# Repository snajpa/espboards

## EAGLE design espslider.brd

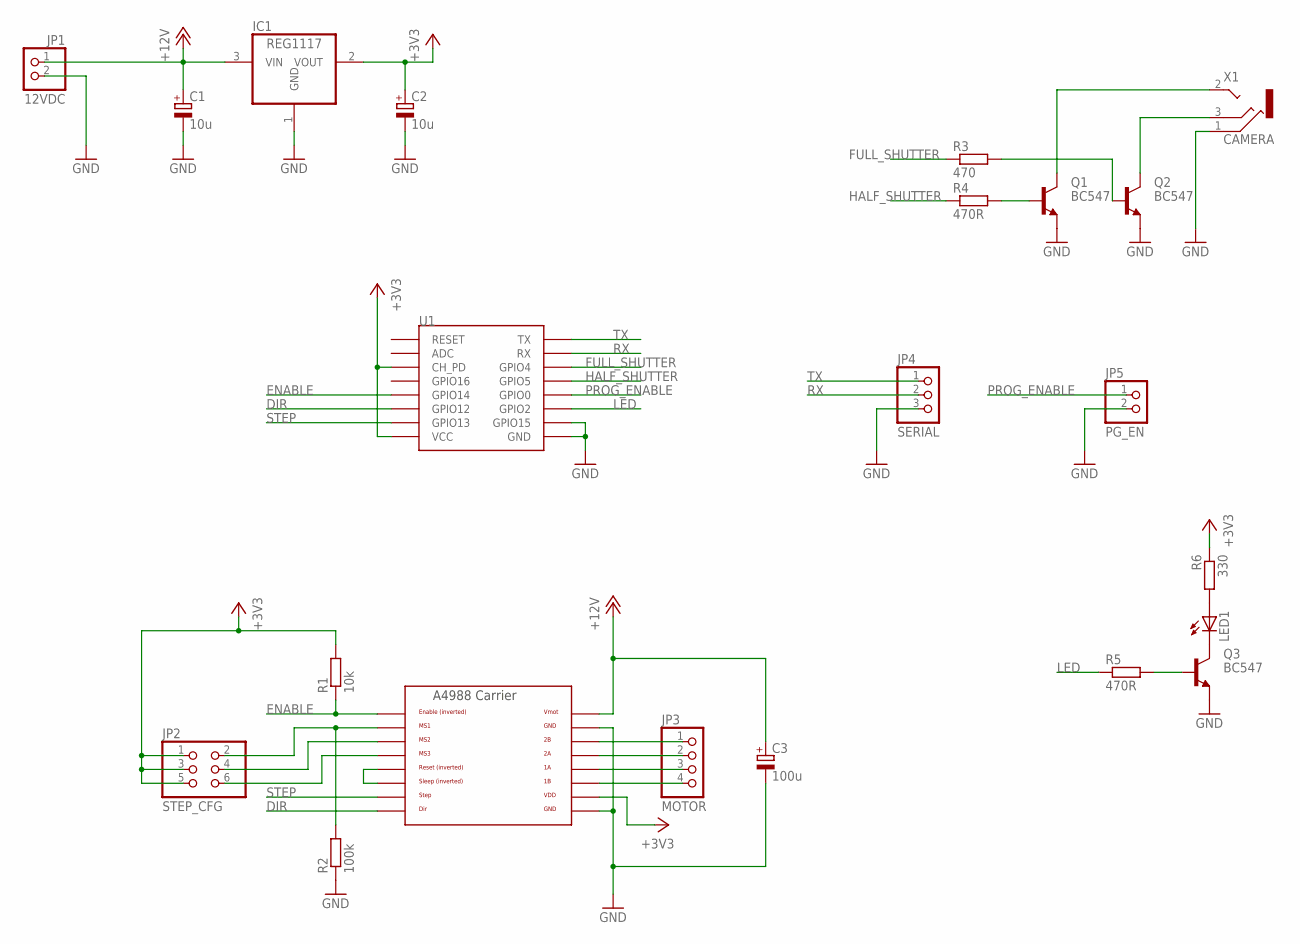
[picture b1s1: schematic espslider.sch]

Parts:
C1, C2: 10u; E5-5; MPN T491C107K010AT
C3: 100u; E5-5
IC1: REG1117; SOT223
JP1: 12VDC; 1X02
JP2: STEP_CFG; 2X03
JP3: MOTOR; 1X04
JP4: SERIAL; 1X03
JP5: PG_EN; 1X02
LED1: LED3MM
Q1, Q2, Q3: BC547; TO92
R1: 10k; 0207/7
R2: 100k; 0207/15
R3: 470; 0207/7
R4, R5: 470R; 0207/7
R6: 330; 0207/7
U1: ESP12SMD; ESP12-SMD
U2: A4988BREAKOUT
X1: CAMERA; 1501_05

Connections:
+3V3: C2.+, IC1.2 (VOUT), JP2.1, JP2.3, JP2.5, R1.2, R6.1, U1.CH_PD, U1.VCC, U2.VDD
+12V: C1.+, C3.+, IC1.3 (VIN), JP1.1, U2.VMOT
DIR: U1.GPIO12, U2.DIR
ENABLE: R1.1, U1.GPIO14, U2.EN
FULL_SHUTTER: R3.1, U1.GPIO4
GND: C1.-, C2.-, C3.-, IC1.1 (GND), JP1.2, JP4.3, JP5.2, Q1.1 (E), Q2.1 (E), Q3.1 (E), R2.1, U1.GND, U1.GPIO15, U2.GND, U2.GND@0 (GND), X1.1
HALF_SHUTTER: R4.1, U1.GPIO5
LED: R5.1, U1.GPIO2
unnamed: Q2.3 (C), X1.3
unnamed: Q2.2 (B), R3.2
unnamed: Q1.2 (B), R4.2
unnamed: Q1.3 (C), X1.2
unnamed: JP2.2, R2.2, U2.MS1
unnamed: JP2.4, U2.MS2
unnamed: JP2.6, U2.MS3
unnamed: LED1.A, R6.2
unnamed: U2.RST, U2.SLP (SLEEP)
unnamed: JP3.1, U2.2B
unnamed: JP3.2, U2.2A
unnamed: JP3.3, U2.1A
unnamed: JP3.4, U2.1B
unnamed: LED1.K (C), Q3.3 (C)
unnamed: Q3.2 (B), R5.2
PROG_ENABLE: JP5.1, U1.GPIO0
RX: JP4.2, U1.RXD0 (RX)
STEP: U1.GPIO13, U2.STEP
TX: JP4.1, U1.TXD0 (TX)

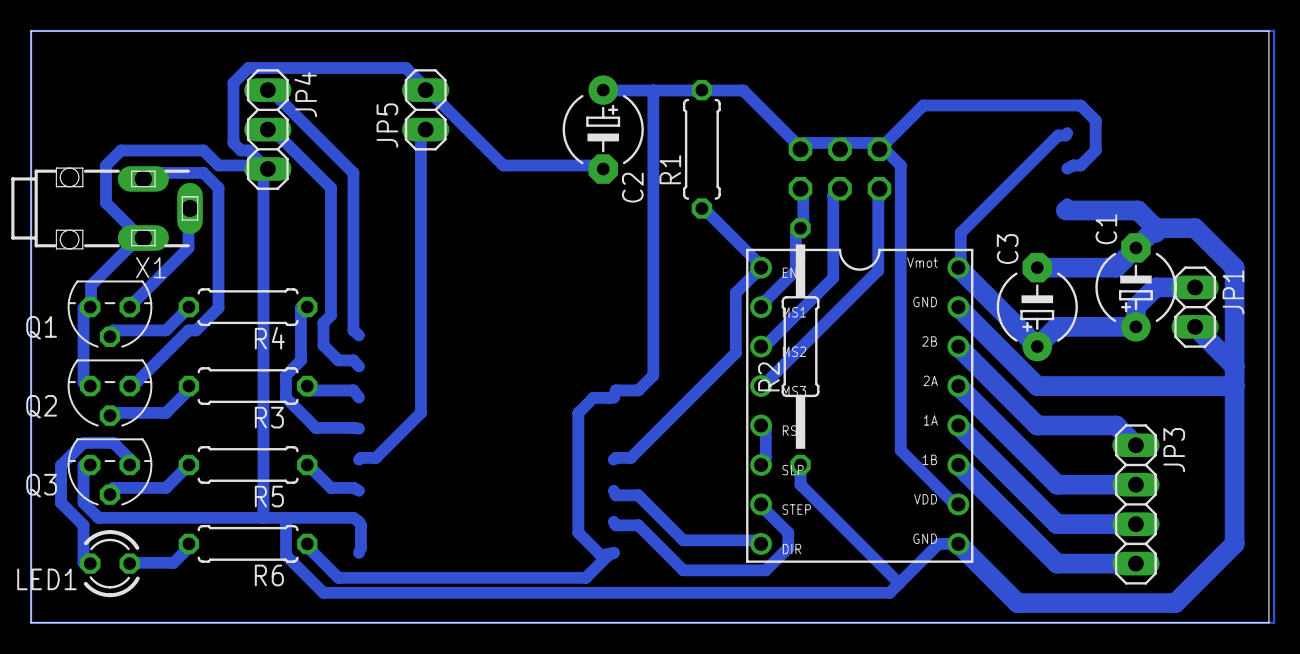
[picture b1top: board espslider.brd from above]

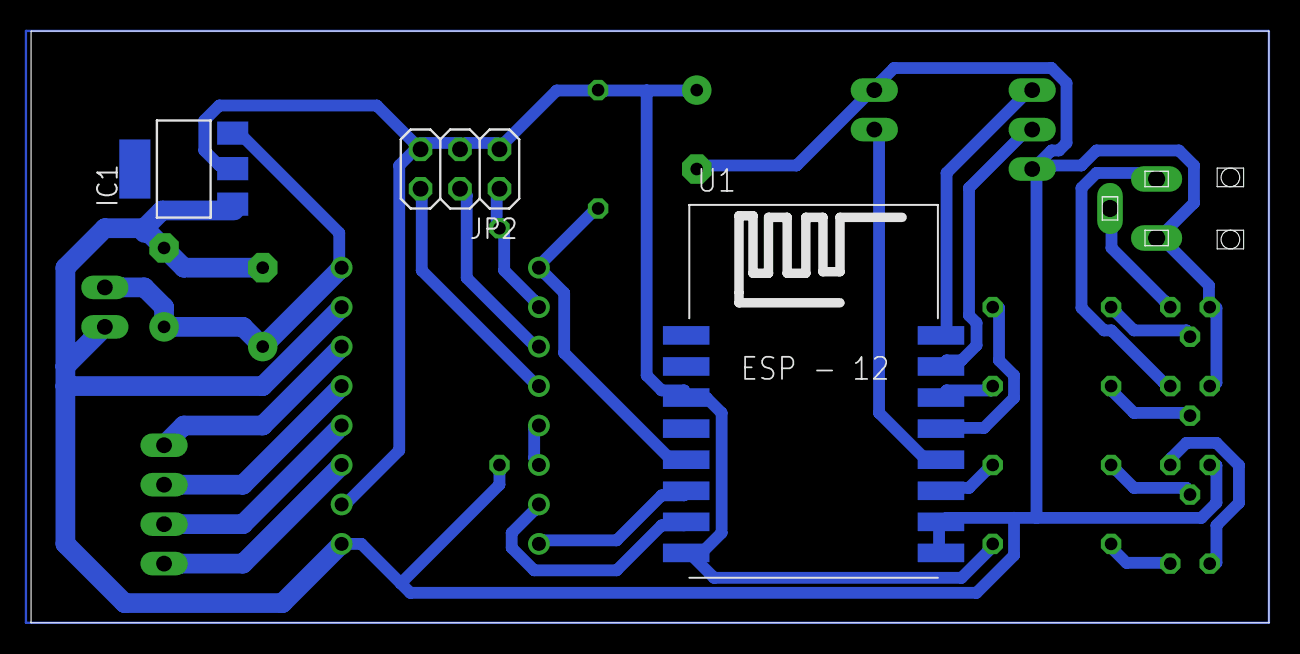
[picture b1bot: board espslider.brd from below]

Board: 2 copper layers, 79.7 x 38.1 mm, 22 parts (3 on the bottom side), 27 nets.

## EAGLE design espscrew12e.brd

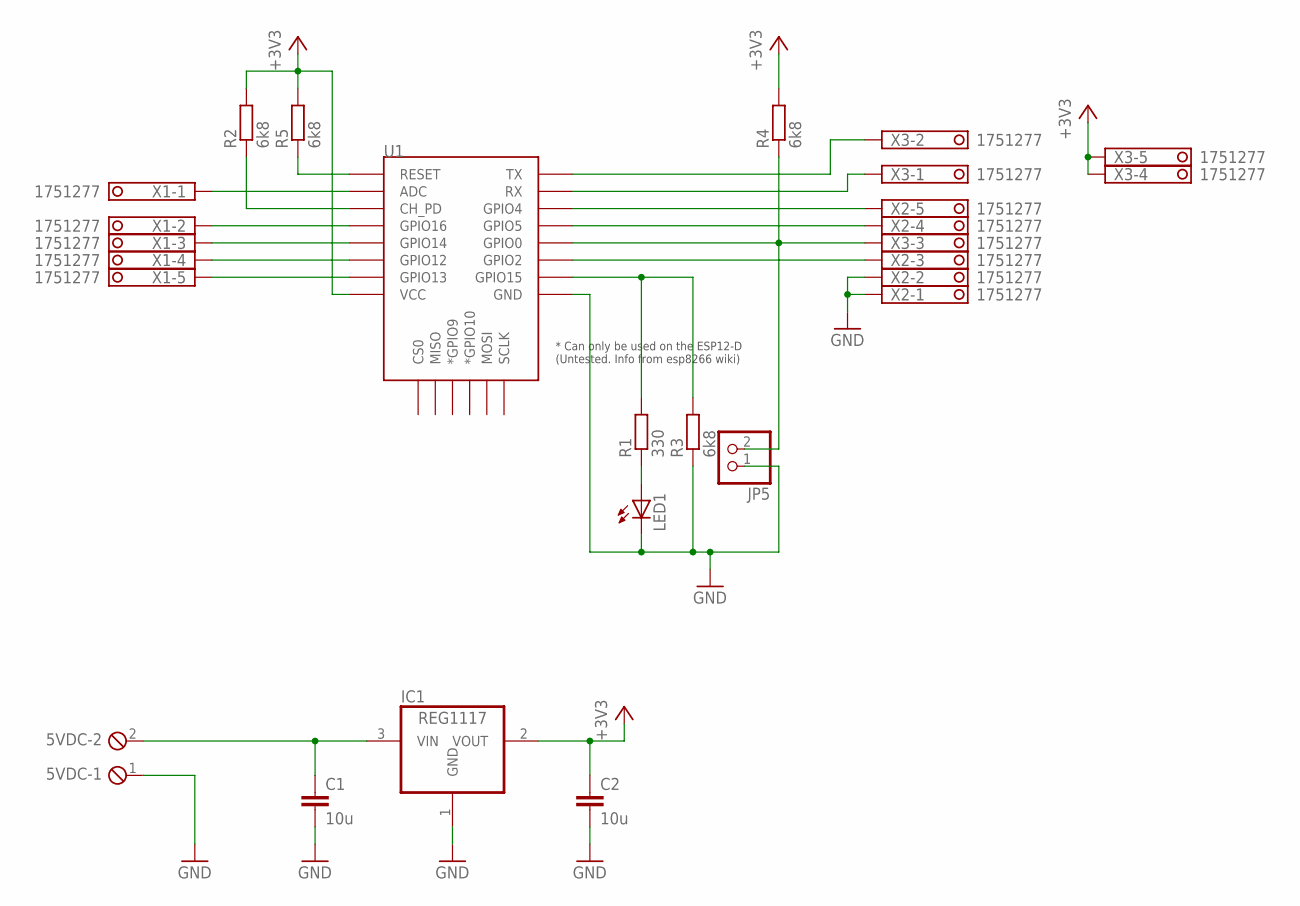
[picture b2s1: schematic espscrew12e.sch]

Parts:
5VDC: MPT2; 2POL254
C1, C2: 10u; C1206K
IC1: REG1117; SOT223
JP5: PINHD-1X2; 1X02
LED1: LEDSML1206; SML1206
R1: 330; R1206
R2, R3, R4, R5: 6k8; R1206
U1: ESP12ESMD; ESP12E-SMD
X1, X2, X3: 1751277

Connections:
+3V3: C2.1, IC1.2 (VOUT), R2.2, R4.2, R5.2, U1.VCC, X3.4, X3.5
GND: 5VDC.1, C1.2, C2.2, IC1.1 (GND), JP5.1, LED1.C, R3.1, U1.GND, X2.1, X2.2
unnamed: 5VDC.2, C1.1, IC1.3 (VIN)
unnamed: LED1.A, R1.1
unnamed: R5.1, U1.RESET
unnamed: U1.ADC, X1.1
unnamed: R2.1, U1.CH_PD
unnamed: U1.GPIO16, X1.2
unnamed: U1.GPIO14, X1.3
unnamed: U1.GPIO12, X1.4
unnamed: U1.GPIO13, X1.5
unnamed: U1.TXD0 (TX), X3.2
unnamed: U1.RXD0 (RX), X3.1
unnamed: U1.GPIO4, X2.5
unnamed: U1.GPIO5, X2.4
unnamed: JP5.2, R4.1, U1.GPIO0, X3.3
unnamed: U1.GPIO2, X2.3
unnamed: R1.2, R3.2, U1.GPIO15

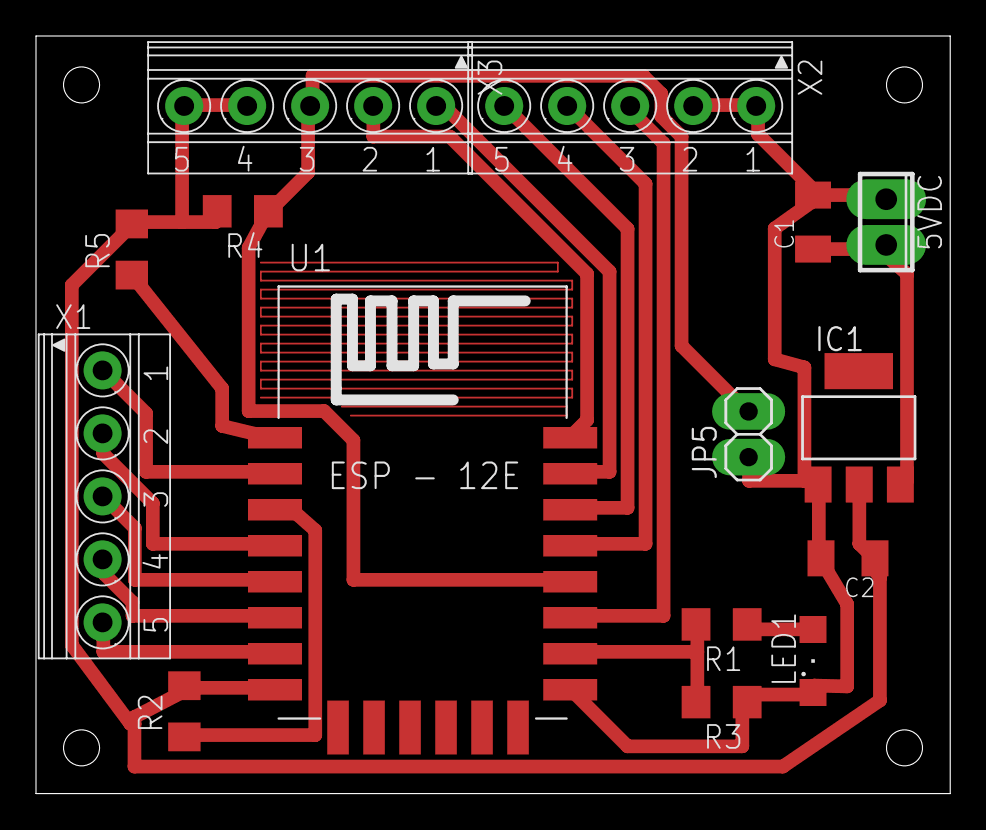
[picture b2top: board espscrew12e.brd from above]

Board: 2 copper layers, 50.8 x 42.1 mm, 15 parts (0 on the bottom side), 18 nets.

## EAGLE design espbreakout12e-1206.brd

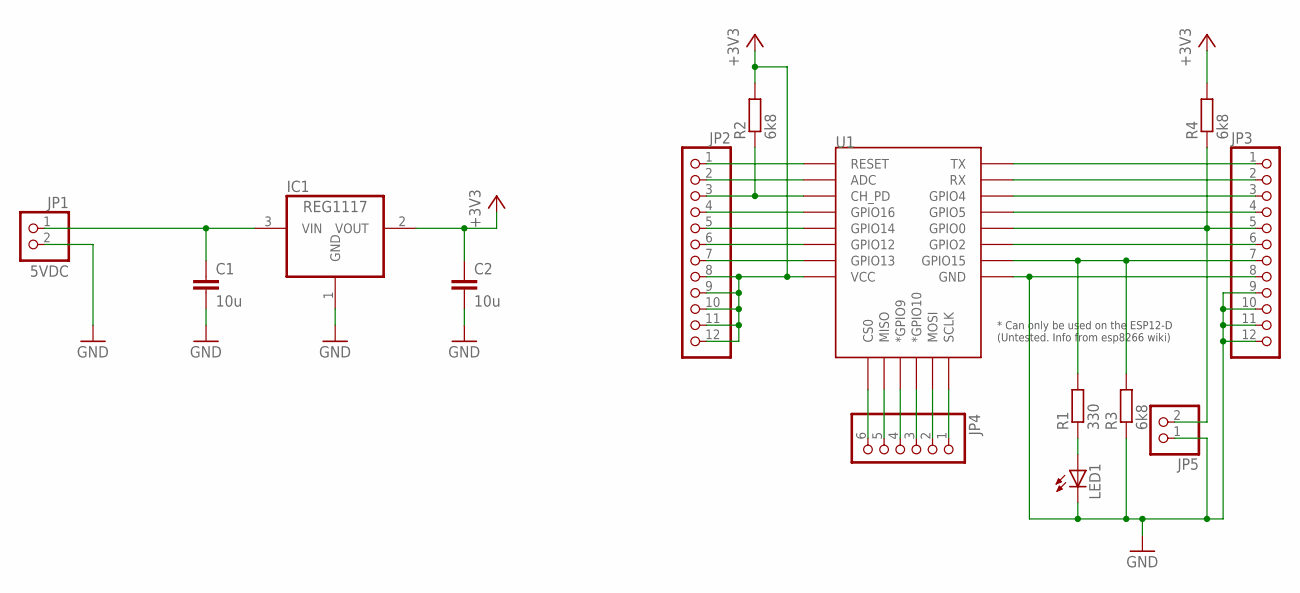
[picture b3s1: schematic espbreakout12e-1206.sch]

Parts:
C1, C2: 10u; C1206K
IC1: REG1117; SOT223
JP1: 5VDC; 1X02
JP2, JP3: PINHD-1X12; 1X12
JP4: PINHD-1X6; 1X06
JP5: PINHD-1X2; 1X02
LED1: LEDSML1206; SML1206
R1: 330; R1206
R2, R3, R4: 6k8; R1206
U1: ESP12ESMD; ESP12E-SMD

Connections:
+3V3: C2.1, IC1.2 (VOUT), JP2.8, JP2.9, JP2.10, JP2.11, JP2.12, R2.2, R4.2, U1.VCC
GND: C1.2, C2.2, IC1.1 (GND), JP1.2, JP3.8, JP3.9, JP3.10, JP3.11, JP3.12, JP5.1, LED1.C, R3.1, U1.GND
unnamed: C1.1, IC1.3 (VIN), JP1.1
unnamed: LED1.A, R1.1
unnamed: JP2.1, U1.RESET
unnamed: JP2.2, U1.ADC
unnamed: JP2.3, R2.1, U1.CH_PD
unnamed: JP2.4, U1.GPIO16
unnamed: JP2.5, U1.GPIO14
unnamed: JP2.6, U1.GPIO12
unnamed: JP2.7, U1.GPIO13
unnamed: JP3.1, U1.TXD0 (TX)
unnamed: JP3.2, U1.RXD0 (RX)
unnamed: JP3.3, U1.GPIO4
unnamed: JP3.4, U1.GPIO5
unnamed: JP3.5, JP5.2, R4.1, U1.GPIO0
unnamed: JP3.6, U1.GPIO2
unnamed: JP3.7, R1.2, R3.2, U1.GPIO15
unnamed: JP4.1, U1.SCLK
unnamed: JP4.2, U1.MOSI
unnamed: JP4.3, U1.GPIO10 (*GPIO10)
unnamed: JP4.4, U1.GPIO9 (*GPIO9)
unnamed: JP4.5, U1.MISO
unnamed: JP4.6, U1.CS0

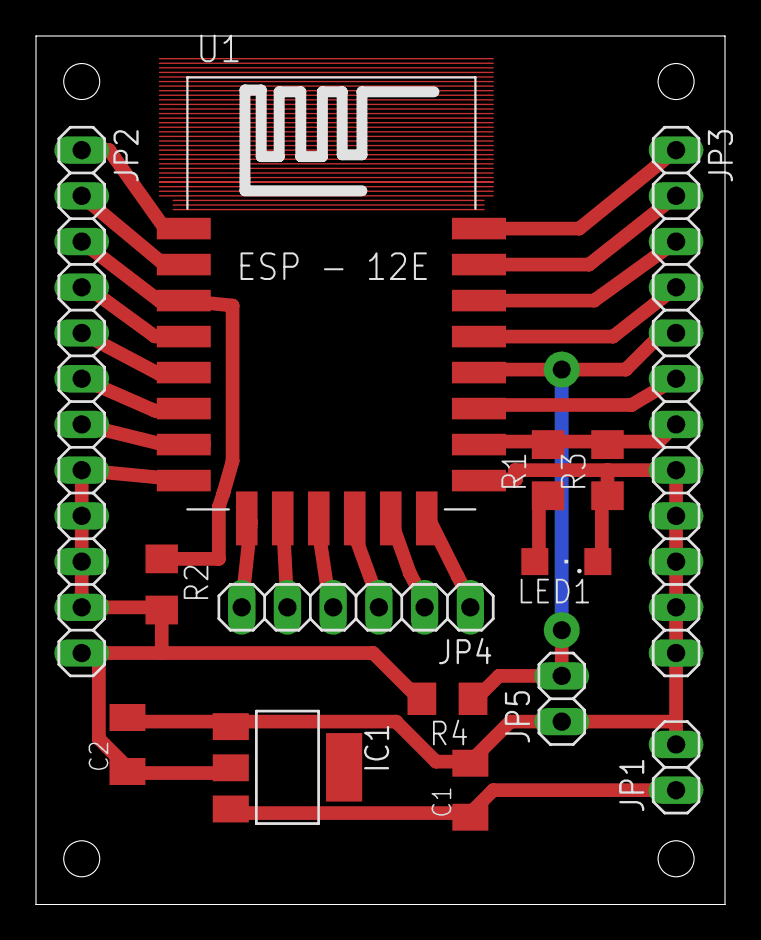
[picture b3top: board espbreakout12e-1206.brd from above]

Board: 2 copper layers, 38.3 x 48.2 mm, 14 parts (0 on the bottom side), 24 nets.

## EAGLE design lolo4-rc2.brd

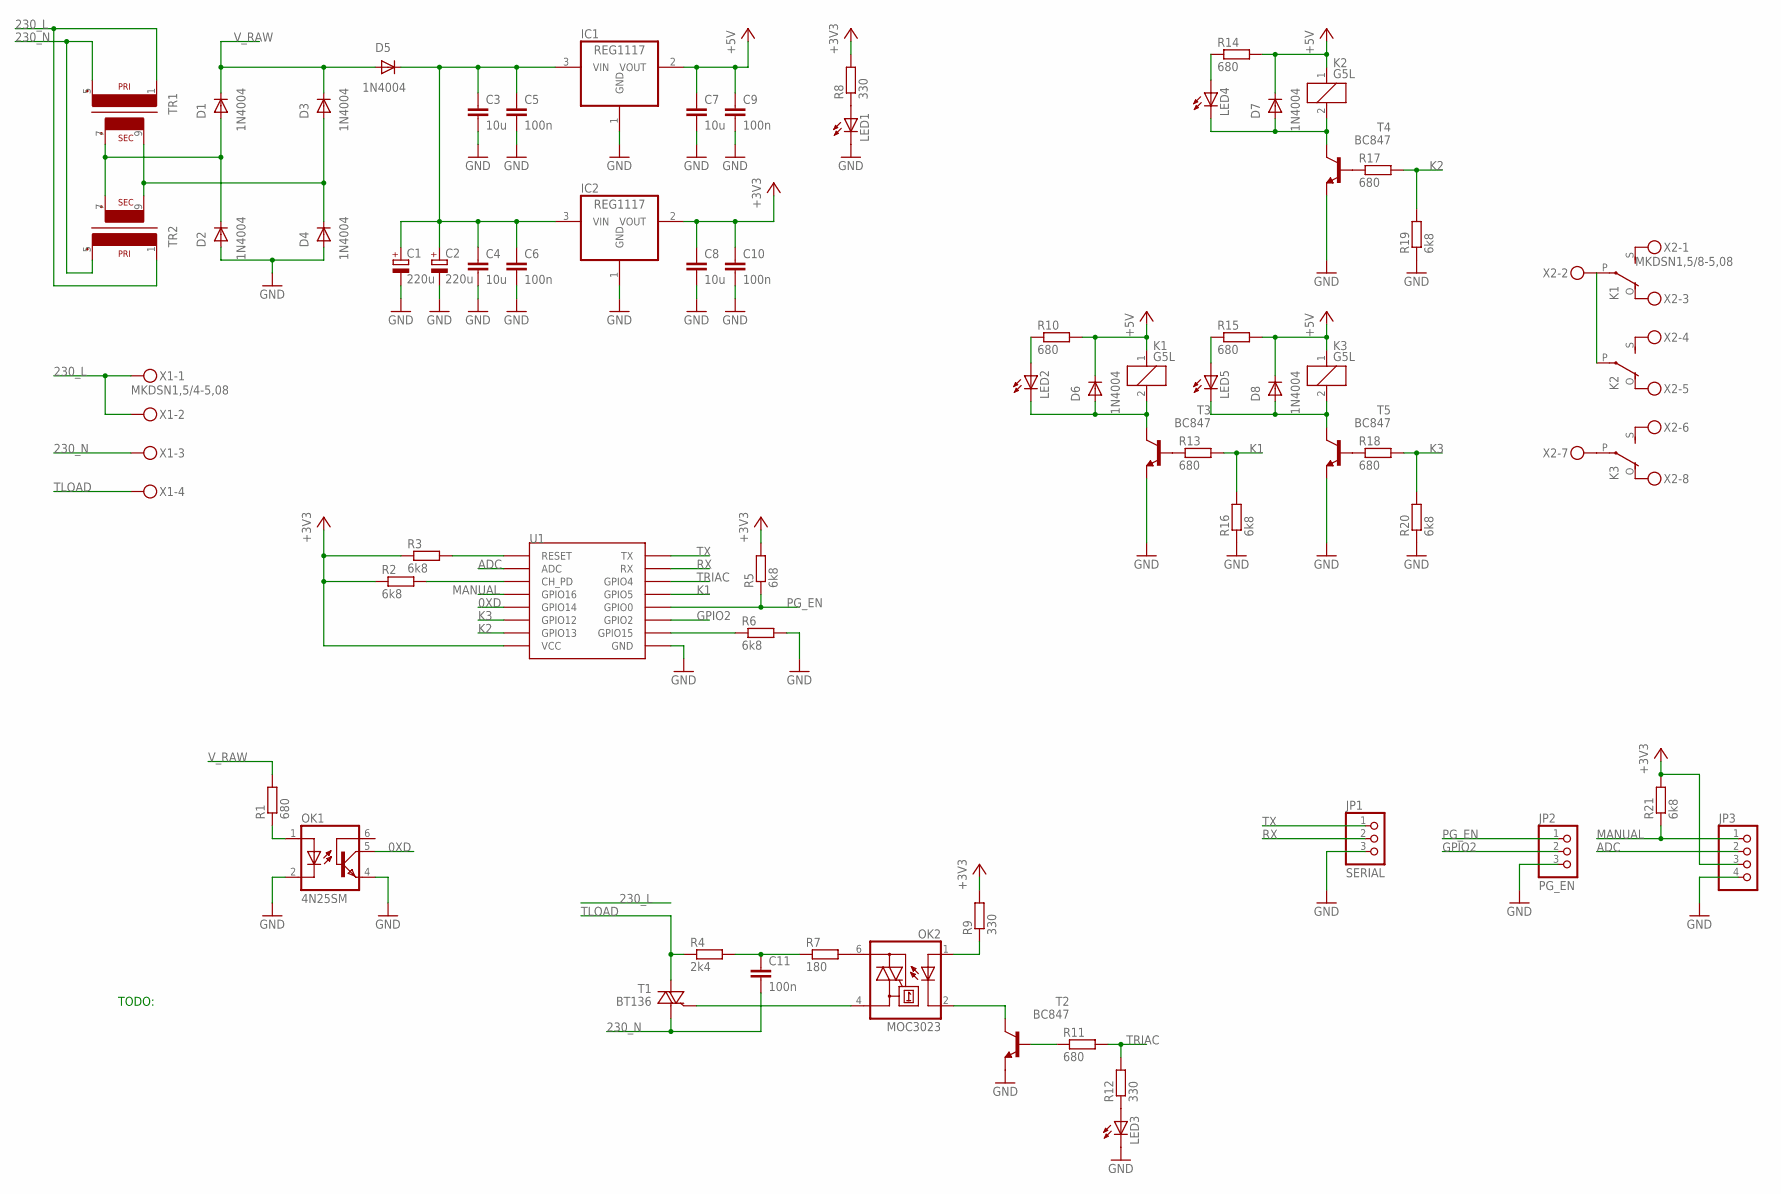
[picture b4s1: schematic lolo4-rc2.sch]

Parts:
C1, C2: 220u; SANYO-OSCON_SMD_E7
C3, C4, C7, C8: 10u; C1206
C5, C6, C9, C10: 100n; C1206
C11: 100n; C150-054X183
D1, D2, D3, D4, D5, D6, D7, D8: 1N4004; DO41-10
IC1, IC2: REG1117; SOT223
JP1: SERIAL; 1X03
JP2: PG_EN; 1X03
JP3: PINHD-1X4; 1X04
K1, K2, K3: G5L; G5LE
LED1, LED2, LED3, LED4, LED5: LEDSML1206; SML1206
OK1: 4N25SM; DIL6-SMD
OK2: MOC3023; DIL6-SMD
R1, R10, R11, R13, R14, R15, R17, R18: 680; R1206
R2, R3, R5, R6, R16, R19, R20, R21: 6k8; R1206
R4: 2k4; 0207/7
R7: 180; 0207/7
R8, R9, R12: 330; R1206
T1: BT136; TO220AB
T2, T3, T4, T5: BC847; SOT23
TR1, TR2: VR11
U1: ESP12SMD; ESP12-SMD
X1: MKDSN1,5/4-5,08
X2: MKDSN1,5/8-5,08

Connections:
0XD: OK1.5 (COL), U1.GPIO14
230_L: TR1.1, TR2.1, X1.1, X1.2
230_N: C11.2, T1.1 (A1), TR1.5 (P2), TR2.5 (P2), X1.3
+3V3: C8.1, C10.1, IC2.2 (VOUT), JP3.3, R2.1, R3.1, R5.2, R8.2, R9.2, R21.2, U1.VCC
+5V: C7.1, C9.1, D6.C, D7.C, D8.C, IC1.2 (VOUT), K1.1, K2.1, K3.1, R10.2, R14.2, R15.2
ADC: JP3.2, U1.ADC
GND: C1.-, C2.-, C3.2, C4.2, C5.2, C6.2, C7.2, C8.2, C9.2, C10.2, D2.A, D4.A, IC1.1 (GND), IC2.1 (GND), JP1.3, JP2.3, JP3.4, LED1.C, LED3.C, OK1.2 (C), OK1.4 (EMI), R6.2, R16.1, R19.1, R20.1, T2.2 (E), T3.2 (E), T4.2 (E), T5.2 (E), U1.GND
GPIO2: JP2.2, U1.GPIO2
K1: R13.2, R16.2, U1.GPIO5
K2: R17.2, R19.2, U1.GPIO13
K3: R18.2, R20.2, U1.GPIO12
MANUAL: JP3.1, R21.1, U1.GPIO16
unnamed: K1.S, X2.1
unnamed: K1.P, K2.P, X2.2
unnamed: K1.O, X2.3
unnamed: K2.S, X2.4
unnamed: K2.O, X2.5
unnamed: K3.P, X2.7
unnamed: K3.S, X2.6
unnamed: LED1.A, R8.1
unnamed: K3.O, X2.8
unnamed: D1.A, D2.C, TR1.7 (S3), TR2.7 (S3)
unnamed: D3.A, D4.C, TR1.9 (S4), TR2.9 (S4)
unnamed: R2.2, U1.CH_PD
unnamed: R6.1, U1.GPIO15
unnamed: R3.2, U1.RESET
unnamed: LED3.A, R12.1
unnamed: R13.1, T3.1 (B)
unnamed: R18.1, T5.1 (B)
unnamed: D7.A, K2.2, LED4.C, T4.3 (C)
unnamed: LED4.A, R14.1
unnamed: R17.1, T4.1 (B)
unnamed: D6.A, K1.2, LED2.C, T3.3 (C)
unnamed: OK1.1 (A), R1.1
unnamed: R11.1, T2.1 (B)
unnamed: D8.A, K3.2, LED5.C, T5.3 (C)
unnamed: LED2.A, R10.1
unnamed: OK2.4 (A1), T1.3 (G)
unnamed: OK2.6 (A2), R7.2
unnamed: C11.1, R4.2, R7.1
unnamed: OK2.2 (C), T2.3 (C)
unnamed: OK2.1 (A), R9.1
unnamed: LED5.A, R15.1
PG_EN: JP2.1, R5.1, U1.GPIO0
RX: JP1.2, U1.RXD0 (RX)
TLOAD: R4.1, T1.2 (A2), X1.4
TRIAC: R11.2, R12.2, U1.GPIO4
TX: JP1.1, U1.TXD0 (TX)
V: C1.+, C2.+, C3.1, C4.1, C5.1, C6.1, D5.C, IC1.3 (VIN), IC2.3 (VIN)
V_RAW: D1.C, D3.C, D5.A, R1.2

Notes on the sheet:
TODO:

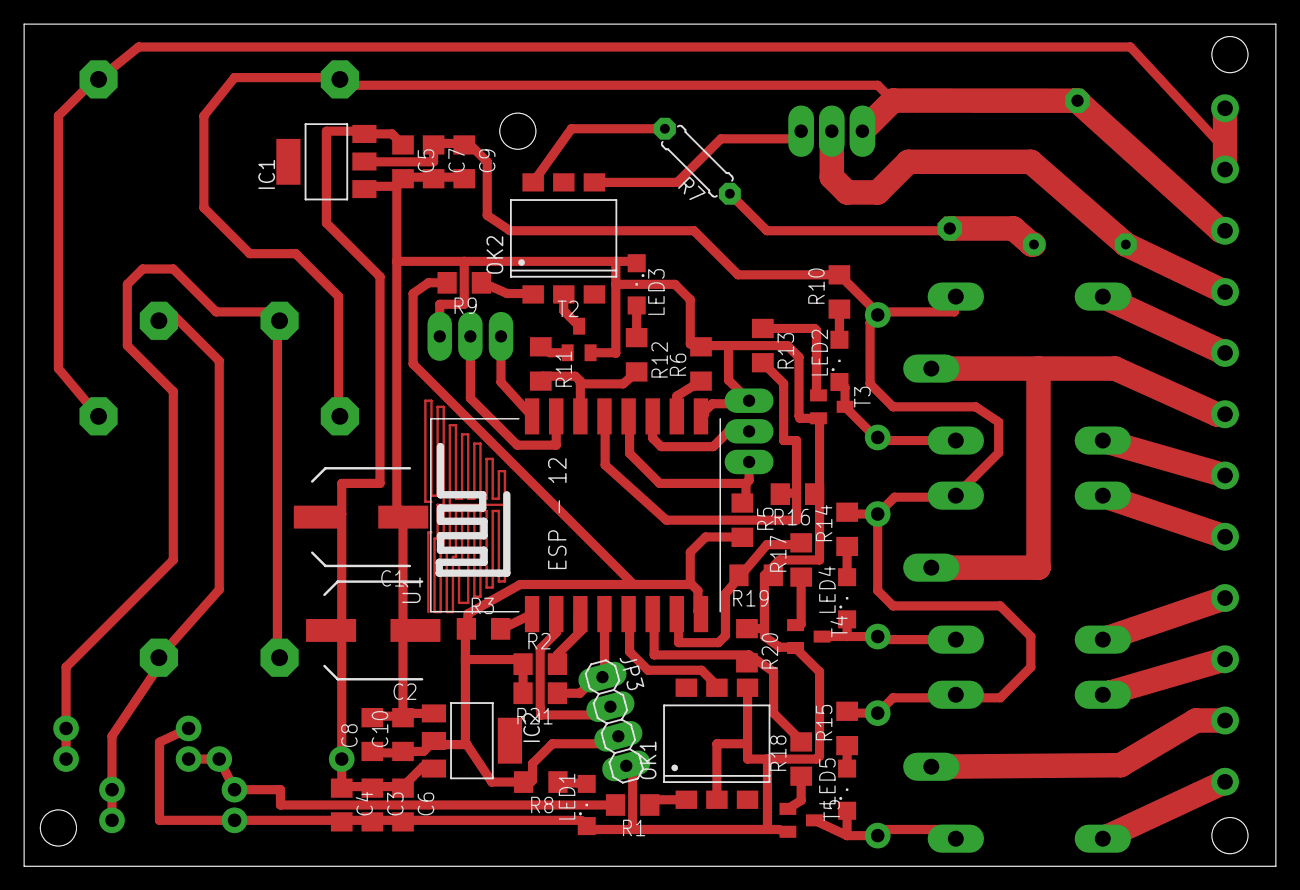
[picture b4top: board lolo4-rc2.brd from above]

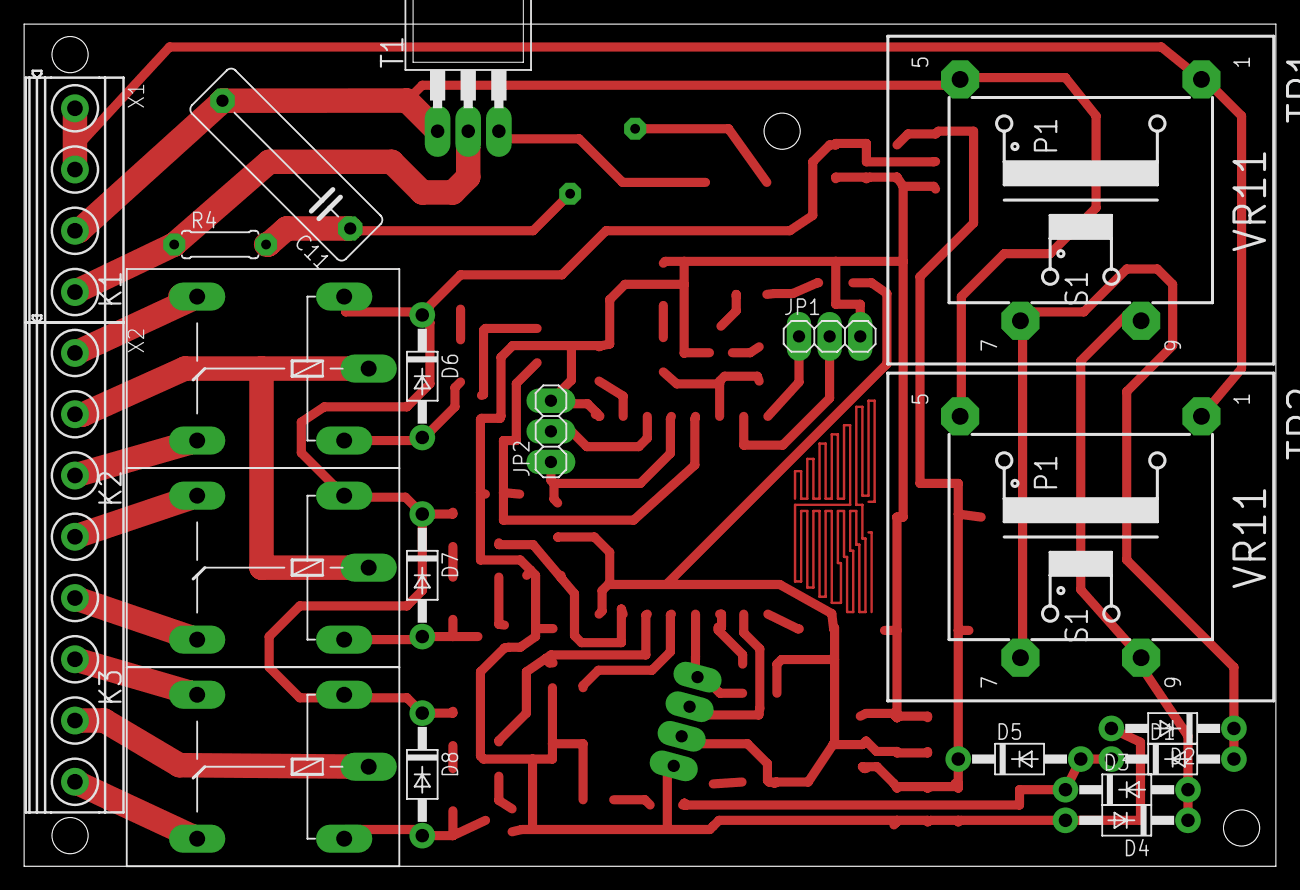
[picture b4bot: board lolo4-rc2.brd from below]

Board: 2 copper layers, 103.8 x 69.8 mm, 65 parts (20 on the bottom side), 50 nets.

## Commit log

2017-01-28 add imported esp8266 modules library
